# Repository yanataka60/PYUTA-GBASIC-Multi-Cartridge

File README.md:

# TOMY ぴゅう太用G-BASIC Multi Cartridge

　「G-BASICのゲームをカートリッジ化する」で作成したROMイメージを初代ぴゅう太で気楽に遊べるようROMイメージをディップスイッチで切り替えられる基板を作ってみました。

　「G-BASICのゲームをカートリッジ化する」https://tms9918.hatenablog.com/entry/2018/02/12/234003

　ゲームアダプタの機能を載せてあるので本体後部の拡張端子に差し込めば使えます。

#### 注)初代ぴゅう太専用です。ぴゅう太mk2、ぴゅう太Jr.では動作しません。ぴゅう太mk2の拡張端子に挿入した場合、ぴゅう太mk2本体が故障する可能性もあり得ます。

　なお、GAL及びROMへ書き込むための機器が別途必要となります。

### 回路図
　KiCadフォルダ内のPYUTA_GBASIC.pdfを参照してください。

[回路図](https://github.com/yanataka60/PYUTA-GBASIC-Multi-Cartridge/blob/main/Kicad/PYUTA_GBASIC.pdf)

### 部品
|番号|品名|数量|備考|
| ------------ | ------------ | ------------ | ------------ |
|J1|50Pカードエッジコネクタ|1|せんごくネット通販 HRS CR22A-50D-2.54DSなど|
|U1|74LS32|1||
|U2|74LS138|1||
|U3-U6|ROM 27512|1～4|最大4個|
|U7|GAL22V10|1||
|U8|RAM 62256相当品|1|32KROM用としてしか使わないなら不要|
|SW1|DIPスイッチ 4P|1|秋月電子通商 EDS104SZなど|
|S1-S2|3Pスライドスイッチ|2|秋月電子通商 SS12D01G4など|
|R1-R6|カーボン抵抗 10KΩ|6||
|C1|電解コンデンサ 16v100uF|1||
|C2-C9|積層セラミックコンデンサ 0.1uF|8||
||28P ICソケット|5||
||24P ICソケット|1|使用は任意|
||16P ICソケット|1|使用は任意|
||14P ICソケット|1|使用は任意|

### GALへの書込み
　cuplフォルダのPYUTACMT.jedをROMライター(TL866II Plus等)を使ってGAL22V10に書き込みます。

### loader.bin
　loaderフォルダのloader.binを後述「ROMイメージ作成方法」で使います。

ソースコードは「G-BASICのゲームをカートリッジ化する」に掲載されています。

　「G-BASICのゲームをカートリッジ化する」https://tms9918.hatenablog.com/entry/2018/02/12/234003

　vdpmemcpy関数で書き込んだだけではVRAMに背景色が設定されないとのことでしたが、試行錯誤の結果bordercolor関数で設定できましたので以下の修正を加えてコンパイルしています。

/* VDP SETUP */の前に次の1行を付加。

  const unsigned char *p = (const unsigned char*)0x8fee;

/* RESTORE VRAM */の前に次の1行を付加。

  bordercolor(*p);

### ROMへの書込み
　後述「ROMイメージ作成方法」で作成したROMイメージを27512の0000h、8000hを先頭アドレスとして書き込みます。

### ROMイメージの切り替え
　DIPスイッチ1番スイッチで0000h、8000hのイメージの切り替え、DIPスイッチ2番、3番スイッチでROMを選択できます。

　最大8種類のROMイメージを切り替え可能です。

### CMT、32K切り替えスイッチ
　スイッチを切り替えることでROMに焼かれているイメージがCMTイメージか、32KROMイメージかを切り替えることができます。

　いぬふとさんのぴゅう太32KROMイメージ用の32KROM Multi Cartridgeを初代ぴゅう太で遊ぶためにはゲームアダプタ相当品が必要ですが、このスイッチを32K側にすることでROMに焼かれた内容を32KROMイメージのゲームと解釈するようになりゲームアダプタ相当品なしでG-BASIC Multi Cartridgeだけで遊べます。

　スイッチの切り替えによるRAM、ROMの割り当ては以下のように変化します。
#### スイッチがCMT側の場合の割り当て
|Address|RAM|ROM|
| ------------ | ------------ | ------------ |
|>0000|||
|>2000|||
|>4000||>4000|
|>6000|>6000||
|>8000||>0000|
|>A000||>2000|
|>C000|>4000||
|>E000|||

　「ぴゅう太の拡張スロットにRAM&ROMカートリッジをつないでみる　その６」より抜粋 https://tms9918.hatenablog.com/entry/2018/01/18/211846

#### スイッチが32K側の場合の割り当て
　32KROM用としてしか使わないならRAMは不要となります。

|Address|RAM|ROM|
| ------------ | ------------ | ------------ |
|>0000|||
|>2000|||
|>4000||>0000|
|>6000||>2000|
|>8000||>4000|
|>A000||>6000|
|>C000|||
|>E000|||

　「ぴゅう太の拡張スロットにRAM&ROMカートリッジをつないでみる　その３」より抜粋 https://tms9918.hatenablog.com/entry/2017/03/09/194928

### ON、OFFスイッチ
　OFFにすることでG-BASIC Multi CartridgeのRAM、ROMの選択信号を非選択状態に固定し、RAM、ROMを切り離します。

　G-BASIC Multi Cartridgeを挿入したまま、カートリッジスロットにカートリッジを挿入して遊べます。

### ぴゅう太BIOS抽出方法
　「G-BASICのゲームをカートリッジ化する」にはぴゅう太のBIOSを抽出する必要があります。

#### 方法1　TINY野郎さんの「ぴゅう太 BIOS吸い出し用ツール」で抽出する。

　「ぴゅう太 BIOS吸い出し用ツール」https://x.com/tiny_yarou/status/886025340400705536

　動画をキャプチャし、出来上がった動画をMovieToBin.exeで変換します。

　私の環境では変換は正常終了したのですが、ところどころデータが化けてしまったようです。

　うまくいけば簡単安全な方法です。

　ちなみにうまく変換できたときに作成されるIPL.ROMのMD5ハッシュ値はa2034c21bd901baceb05d74a809dd990になります。

　コマンドプロンプトから「CertUtil -hashfile IPL.ROM md5」を実行して確認してみてください。

#### 方法2　本体内からROMを抜きROMライターでROMの内容をダンプする。

　確実な方法ですが、カバーを外す、ROMを引き抜く、ROMをダンプする、ROMを戻す、カバーを戻すという過程でぴゅう太本体及びROMを破壊してしまう可能性があります。自己責任でお願いします。

　本体裏のねじ6本を外します。

.JPG)

　本体カバーを上に持ち上げるとカバーは外れますが、キーボードとのケーブルがフィルムケーブルですので損傷しないよう静かに持ち上げてください。

.JPG)

　フィルムケーブルも外せると思うのですがうちの機体がかなりきつく入っており抜くと損傷しそうなのでそのまま作業を行うことにしました。

　外せるなら外してしまったほうが作業は楽です。

　コの字型の金具は手前に引き抜けます。

.JPG)

　シールド版を外すにはは6個のねじを外します。

.JPG)

.JPG)

.JPG)

.JPG)

　システムと書かれたROMを引き抜き内容をダンプ、IPL.ROMの名前で保存します。

　キーボードを接続しているフィルムケーブルが緩んでいないか確認しつつ逆の手順で戻していきます。

### ROMイメージ作成方法
　MAMEのデバッガを使ってVRAMのDUMPをする方法は「G-BASICのゲームをカートリッジ化する」のページに記載がありますが、もうちょっと解説しておきます。

#### 1 MAMEの導入
　[MAME公式ページ]https://www.mamedev.org/

　mamexxxxx_64bit.exeをダウンロードし、実行すると解凍するフォルダ名を聞かれますのでそのままExtractを押すとmamexxxxx_64bit.exeのあるフォルダに解凍されます。

　ぴゅう太から抽出したIPL.ROMをtutor1.binという名前でコピーします。

　tutor1.binをpyuuta.zipという名前で圧縮します。

　mameを解凍したフォルダ中のromsフォルダにpyuuta.zipをコピーします。

　後述のROM書き込みイメージデータの作成に必要になるのでぴゅう太から抽出したIPL.ROM(0000h～7FFFh)のうち、4000h～4FFFhをバイナリエディタで抽出してbios.binとして保存しておきます。

#### 2 G-BASICのプログラムをwavファイルに変換
　日本語G-BASICシミュレータ for Windowsでプログラムを作成した場合には、DumpListEditorを使ってwavファイルに変換します。

　[日本語G-BASICシミュレータ for Windows]https://nrtdrv.sakura.ne.jp/gbasic/

　[DumpListEditor]https://bugfire2009.ojaru.jp/download.html#dleditor

#### 3 mameのデバックモードでVRAMイメージを抽出
　mame.exeと同じフォルダに変換したwavファイル(例としてtetris.wav)をコピーし、コマンドプロンプトから次の命令を実行します。

　mame.exe pyuuta -ui_active -debug -resolution 512x384 -cass tetris.wav

　mameがデバッグモードで起動します。

　メニューバーから「Media」をクリック、「Cassette(cass):tetris.wav」をクリック、「Pause/Stop」をクリックします。

　メニューバーから「Debug」をクリック、「Run」をクリックします。

　ぴゅう太が起動するのでエミュレーターウィンドウで一回クリックしてから何かキーを押します。

　G-BASICを起動させ、「10 ｵﾜﾘ」等でモニターモードに入ります。

　「ﾛｰﾄﾞ」と入力して実行します。

　ファイル名を入力します。

　メニューバーから「Media」をクリック、「Cassette(cass):tetris.wav」をクリック、「Play」をクリックします。

　「ﾃﾝｿｳ ｵﾜﾘ」と表示されるまで待ちます。プログラムの大きさにかかわらず11分30秒ほどかかります。

　デバッグウィンドウのコマンド入力欄で一回クリックしてカーソルを移動します。

　save ram.bin,F000:maincpu,100

　saved vram1.bin,0000:tms9928a,1000

　saved vram2.bin,1000:tms9928a,3000

　をそれぞれ実行します。

　mameのバージョンによってコマンドの書式が違う場合がありますので、もしエラー等表示されSAVE出来ない場合はHelp Memoryを実行してsave、savedのパラメータ入力方法を確認してください。

#### 4 ROM書き込みイメージデータの作成
　作成されたram.bin、vram1.bin、vram2.binとこのプロジェクト「PYUTA-GBASIC-Multi-Cartridge」の「loader」フォルダ中のloader.bin、先ほどIPL.ROMから抽出したbios.binを同じフォルダに置き、そのフォルダからコマンドプロンプトを起動し、次のコマンドでファイルを連結します。

　copy /b loader.bin + ram.bin + vram1.bin + bios.bin + vram2.bin PROG.ROM

#### 5 ROMへの書き込み
　PROG.ROMを27512の0000h、8000hを先頭アドレスとして書き込みます。

## 謝辞
　「G-BASICのゲームをカートリッジ化する」を公開してくださったたなむ様、ありがとうございます。

　ぴゅう太の解析情報を公開してくださっているEnri様、ありがとうございます。

## 追記
2025.4.27 R7のシルク印刷を追加。32KROM用としてしか使わないならRAMが不要であることを追記。

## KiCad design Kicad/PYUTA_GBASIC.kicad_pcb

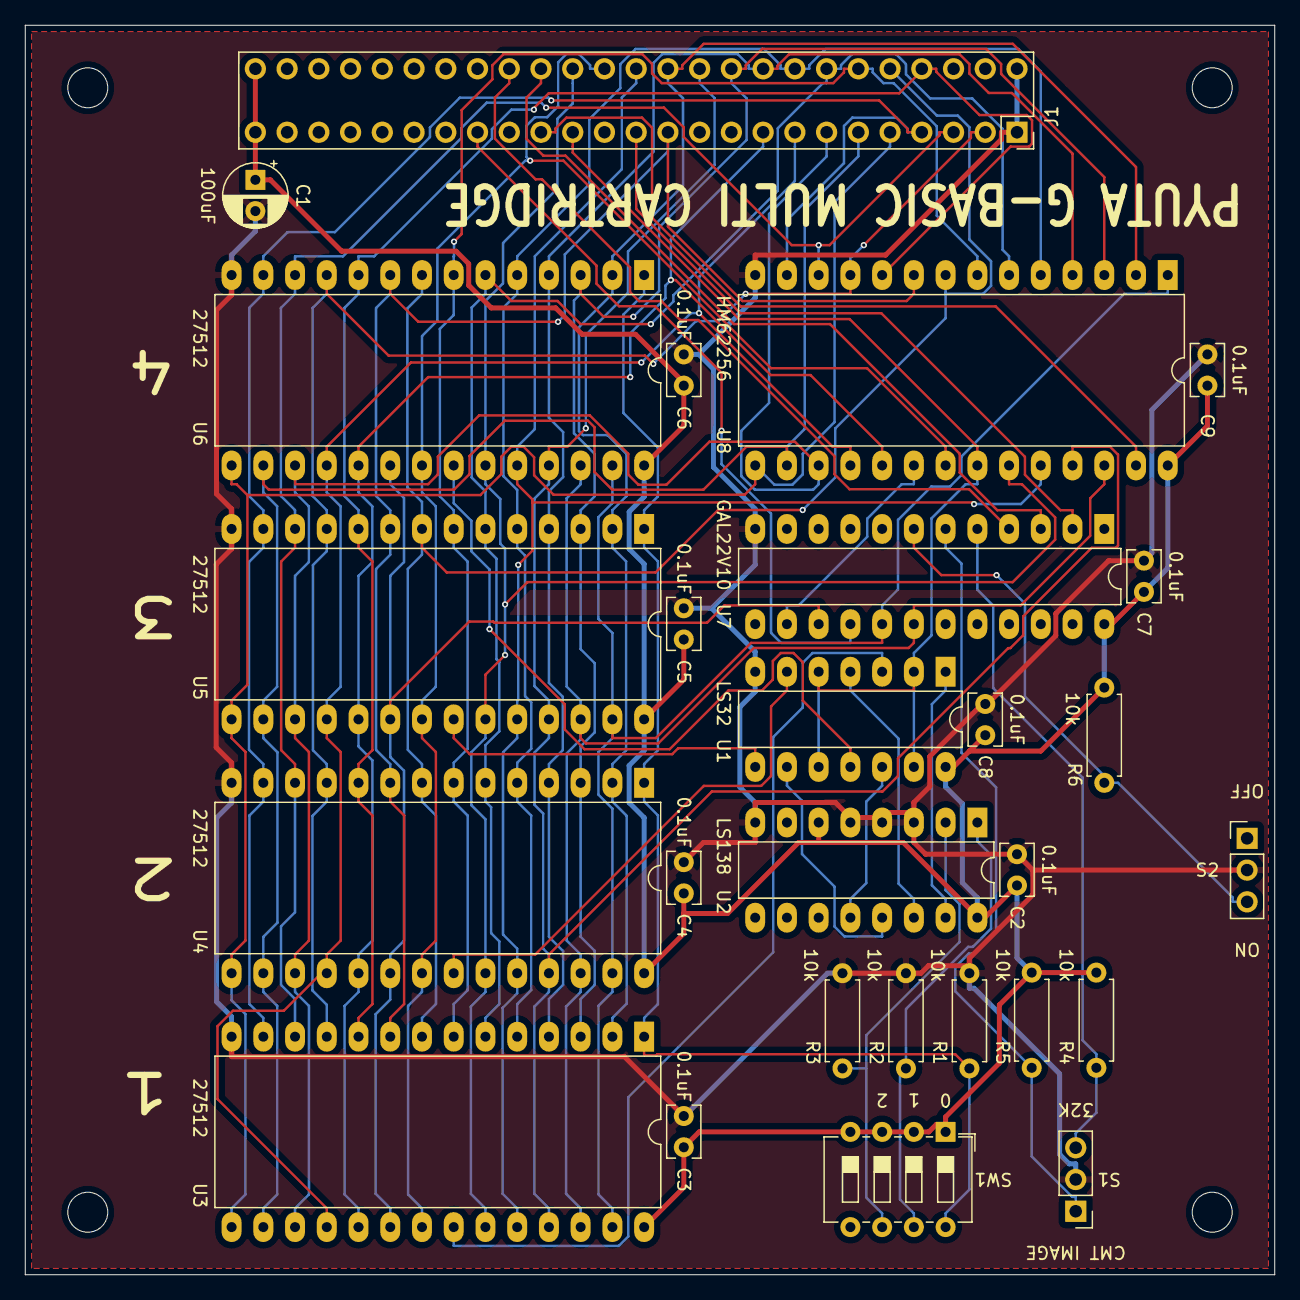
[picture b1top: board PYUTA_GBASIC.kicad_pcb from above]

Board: 2 copper layers, 100.0 x 100.0 mm, 31 parts (0 on the bottom side), 47 nets.

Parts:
C1: 100uF; CP_Radial_D5.0mm_P2.50mm
C2, C3, C4, C5, C6, C7, C8, C9: 0.1uF; C_Rect_L4.0mm_W2.5mm_P2.50mm
J1: Conn_02x25_Odd_Even; PinSocket_2x25_P2.54mm_Vertical
MH1, MH2, MH3, MH4: MountingHole_3.2mm_M3
R1, R2, R3, R4, R5, R6: 10k; R_Axial_DIN0207_L6.3mm_D2.5mm_P7.62mm_Horizontal
S1, S2: SLIDE_SWITCH_3P; PinHeader_1x03_P2.54mm_Vertical
SW1: SW_DIP_x04; SW_DIP_SPSTx04_Slide_6.7x11.72mm_W7.62mm_P2.54mm_LowProfile
U1: 74LS32; DIP-14_W7.62mm_LongPads
U2: 74LS138; DIP-16_W7.62mm_LongPads
U3, U4, U5, U6: 27C512; DIP-28_W15.24mm_LongPads
U7: GAL22V10; DIP-24_W7.62mm_LongPads
U8: HM62256BLP; DIP-28_W15.24mm_LongPads

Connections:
+5V: C1.1, C2.2, C3.2, C4.2, C5.2, C6.2, C7.2, C8.1, C9.2, J1.49, J1.50, R4.1, R5.1, R6.1, SW1.1, SW1.2, SW1.3, SW1.4, U1.14, U2.6, U2.16, U3.28, U4.28, U5.28, U6.28, U7.24, U8.28
/A0: J1.34, U7.4
/A0_n: U3.27, U4.27, U5.27, U6.27, U7.17, U8.1
/A1: J1.32, U7.3
/A2: J1.25, U7.2
/A2_n: U3.26, U4.26, U5.26, U6.26, U7.18, U8.26
/A3: J1.24, U3.2, U4.2, U5.2, U6.2, U8.2
/A4: J1.30, U3.23, U4.23, U5.23, U6.23, U8.23
/A5: J1.28, U3.21, U4.21, U5.21, U6.21, U8.21
/A6: J1.26, U3.24, U4.24, U5.24, U6.24, U8.24
/A7: J1.22, U3.25, U4.25, U5.25, U6.25, U8.25
/A8: J1.20, U3.3, U4.3, U5.3, U6.3, U8.3
/A9: J1.18, U3.4, U4.4, U5.4, U6.4, U8.4
/A10: J1.16, U3.5, U4.5, U5.5, U6.5, U8.5
/A11: J1.14, U3.6, U4.6, U5.6, U6.6, U8.6
/A12: J1.12, U3.7, U4.7, U5.7, U6.7, U8.7
/A13: J1.10, U3.8, U4.8, U5.8, U6.8, U8.8
/A14: J1.23, U3.9, U4.9, U5.9, U6.9, U8.9
/A15: J1.8, U3.10, U4.10, U5.10, U6.10, U8.10
/CE2_n: U3.20, U4.20, U5.20, U6.20, U7.15
/CE_n: U7.14, U8.20
/D0: J1.17, U3.19, U4.19, U5.19, U6.19, U8.19
/D1: J1.15, U3.18, U4.18, U5.18, U6.18, U8.18
/D2: J1.13, U3.17, U4.17, U5.17, U6.17, U8.17
/D3: J1.11, U3.16, U4.16, U5.16, U6.16, U8.16
/D4: J1.9, U3.15, U4.15, U5.15, U6.15, U8.15
/D5: J1.7, U3.13, U4.13, U5.13, U6.13, U8.13
/D6: J1.5, U3.12, U4.12, U5.12, U6.12, U8.12
/D7: J1.3, U3.11, U4.11, U5.11, U6.11, U8.11
/SELEXM: J1.35, U7.16
/~DBIN: J1.29, U1.2, U1.5, U1.10, U1.13, U8.22
/~WE: J1.31, U8.27
GND: C1.2, C2.1, C3.1, C4.1, C5.1, C6.1, C7.1, C8.2, C9.1, J1.1, J1.2, R1.2, R2.2, R3.2, S1.2, S2.2, U1.7, U2.3, U2.4, U2.5, U2.8, U3.14, U4.14, U5.14, U6.14, U7.12, U8.14
unnamed: R1.1, SW1.8, U3.1, U4.1, U5.1, U6.1
unnamed: R2.1, SW1.7, U2.1
unnamed: R3.1, SW1.6, U2.2
unnamed: R4.2, S1.3, U7.5
unnamed: R5.2, S1.1, U7.6
unnamed: R6.2, S2.3, U7.7
unnamed: U1.1, U2.15
unnamed: U1.3, U3.22
unnamed: U1.4, U2.14
unnamed: U1.6, U4.22
unnamed: U1.8, U5.22
unnamed: U1.9, U2.13
unnamed: U1.11, U6.22
unnamed: U1.12, U2.12
